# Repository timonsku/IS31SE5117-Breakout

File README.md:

IS31SE5117-Breakout
===

ISSI IS31SE5117 / IS32SE5117 Touch IC breakout.

Untested, following schematic in datasheet.

https://www.lumissil.com/assets/pdf/core/IS31SE5117_DS.pdf

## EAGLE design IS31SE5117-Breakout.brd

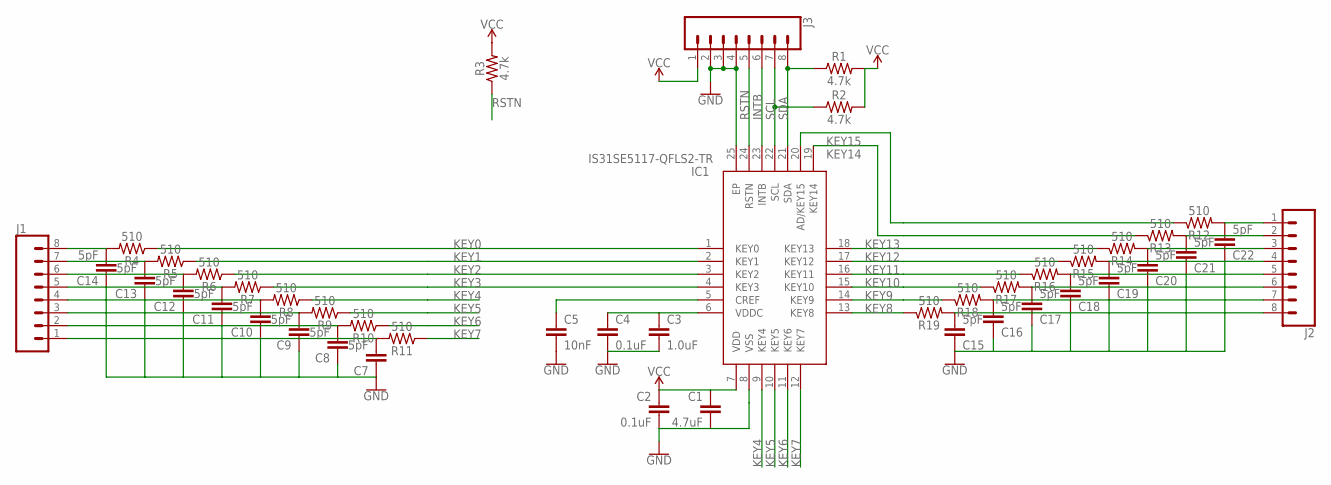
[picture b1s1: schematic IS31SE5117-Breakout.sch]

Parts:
C1: 4.7uF; 0603
C2, C4: 0.1uF; 0603
C3: 1.0uF; 0603
C5: 10nF; 0603
C7, C8, C9, C10, C11, C12, C13, C14, C15, C16, C17, C18, C19, C20, C21, C22: 5pF; 0603
IC1: IS31SE5117-QFLS2-TR; QFN50P400X400X65-25N
J1, J2, J3: CONN_08LONGPADS; 1X08_LONGPADS
R1, R2, R3: 4.7k; 0603
R4, R5, R6, R7, R8, R9, R10, R11, R12, R13, R14, R15, R16, R17, R18, R19: 510; 0603

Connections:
GND: C1.2, C2.2, C3.2, C4.2, C5.2, C7.1, C8.1, C9.1, C10.1, C11.1, C12.1, C13.1, C14.1, C15.1, C16.1, C17.1, C18.1, C19.1, C20.1, C21.1, C22.1, IC1.8 (VSS), IC1.25 (EP), J3.2, J3.3, J3.4
INTB: IC1.23 (INTB), J3.6
KEY0: IC1.1 (KEY0), R4.1
KEY1: IC1.2 (KEY1), R5.1
KEY2: IC1.3 (KEY2), R6.1
KEY3: IC1.4 (KEY3), R7.1
KEY4: IC1.9 (KEY4), R8.1
KEY5: IC1.10 (KEY5), R9.1
KEY6: IC1.11 (KEY6), R10.1
KEY7: IC1.12 (KEY7), R11.1
KEY8: IC1.13 (KEY8), R19.1
KEY9: IC1.14 (KEY9), R18.1
KEY10: IC1.15 (KEY10), R17.1
KEY11: IC1.16 (KEY11), R16.1
KEY12: IC1.17 (KEY12), R15.1
KEY13: IC1.18 (KEY13), R14.1
KEY14: IC1.19 (KEY14), R13.1
KEY15: IC1.20 (AD/KEY15), R12.1
unnamed: C14.2, J1.8, R4.2
unnamed: C13.2, J1.7, R5.2
unnamed: C12.2, J1.6, R6.2
unnamed: C11.2, J1.5, R7.2
unnamed: C10.2, J1.4, R8.2
unnamed: C9.2, J1.3, R9.2
unnamed: C7.2, J1.1, R11.2
unnamed: C8.2, J1.2, R10.2
unnamed: C22.2, J2.1, R12.2
unnamed: C21.2, J2.2, R13.2
unnamed: C20.2, J2.3, R14.2
unnamed: C19.2, J2.4, R15.2
unnamed: C18.2, J2.5, R16.2
unnamed: C3.1, C4.1, IC1.6 (VDDC)
unnamed: C5.1, IC1.5 (CREF)
unnamed: C17.2, J2.6, R17.2
unnamed: C15.2, J2.8, R19.2
unnamed: C16.2, J2.7, R18.2
RSTN: IC1.24 (RSTN), J3.5, R3.1
SCL: IC1.22 (SCL), J3.7, R2.1
SDA: IC1.21 (SDA), J3.8, R1.1
VCC: C1.1, C2.1, IC1.7 (VDD), J3.1, R1.2, R2.2, R3.2

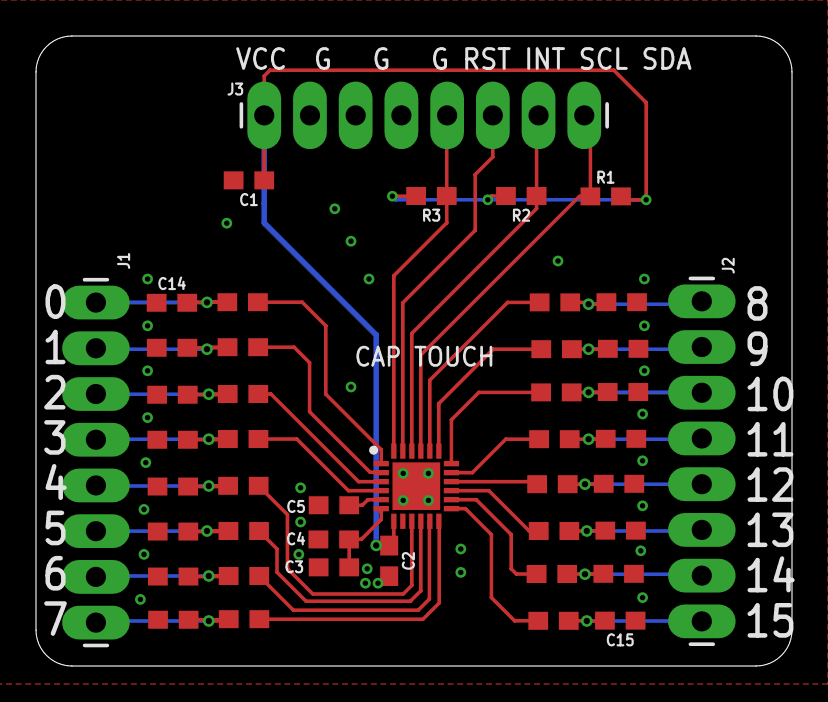
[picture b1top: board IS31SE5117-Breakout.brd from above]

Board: 2 copper layers, 42.0 x 35.0 mm, 44 parts (0 on the bottom side), 40 nets.

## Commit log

2023-05-05 readme

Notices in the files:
parts and their libraries:
SparkFun-Capacitors: Licensing: Creative Commons ShareAlike 4.0 International - https://creativecommons.org/licenses/by-sa/4.0
